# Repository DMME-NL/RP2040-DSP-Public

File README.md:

# 🎸✨ RP2040-DSP: Multi-Effect 24-bit Audio Processor

## 🧩 Summary

RP2040-DSP is a fully modular 24-bit stereo audio effects processor built on the Raspberry Pi RP2040 microcontroller. It is designed to run real-time audio effects for guitar and other instruments, including cabinet simulation for headphone or direct recording use.

The firmware architecture is modular, supporting multiple effects that can be stacked and configured flexibly.

---

## 🎛️ Features & Functionality

- **24-bit stereo signal path** at 48 kHz.
- **Up to 3 simultaneous effects**, each fully configurable and ordered in series.
- Modular effect system with easy header-based integration.
- Real-time parameter control via 6 potentiometers and rotary encoder.
- OLED display for clear feedback and editing.
- Footswitch-controlled bypass and slot toggling.
- Tap-tempo support for modulation and delay-based effects.
- VU meter and signal level visualization.
- Two expression pedal inputs:
  - One dedicated to master volume.
  - One assignable to any effect parameter.

> **Note:** Total number of simultaneous effects is limited by to CPU resources and their type.
> Some features, like MIDI and expression pedal, have not been implemented as of now.

---

## 🎚️ Available Effects

### Modulation

- **Chorus:** 1, 2, or 3 short modulated delay lines with optional stereo spread via phase offset.
- **Flanger:** Single short modulated delay with optional stereo phase offset.
- **Phaser:** Multi-stage all-pass filter network with optional stereo phase offset.
- **Tremolo:** Stereo amplitude modulation with optional stereo phase offset.

### Time-based

- **Delay:** Long stereo delay with different signal path and feedback modes, uses SPI RAM buffering. 
- **Reverb:** Hall / room type reverb based on comb and all-pass filters with modualr buffer size.

### Tone shaping

- **EQ:** Multi-band EQ similar to a guitar tone-stack. Includes range control for mid frequency.

### Dynamic

- **Compressor:** Adjustable threshold, ratio, attack, release, and makeup gain.
- **Distortion, Overdrive, Fuzz:** Various analog-inspired waveshaping algorithms with tone filtering similar to the EQ.

### Speaker & Preamp simulation

- **Cabinet Sim (Speaker Sim):** Parametric approximation of guitar cabinet. Includes multiple controls for tone shaping.
- **Preamp:** Simulates preamp coloration and dynamic shaping (Marshall, VOX, Fender).

### Work-in-Progress

- **Vibrato:** Pure pitch modulation using short-time delay interpolation.

---

## ⚡ Software Architecture and Design Choices

- **Header-based modularity:** Each effect is self-contained in its own header file (`*.h`), following a consistent structure:
  - `init_*()`
  - `load_*_parms_from_memory()`
  - `update_*_params_from_pots()`
  - `process_audio_*_sample()`
- **Pot and memory sync:** Parameters load from stored memory and dynamically update when pots change. Holding down the TAP button for 5 seconds stores all the effects and settings to flash, so they can be receovered after power-down.
- **Optimized math:** Using fixed point math and lightweight approximations, reducing CPU usage without harming audio quality.
- **Dual-core structure:**
  - **Core 0:** Dedicated to real-time audio sample processing.
  - **Core 1:** Handles UI, pot reading, OLED updates.
- **SPI RAM (APS6404L):** Used for long delay lines, minimizing local RAM usage.

> **Note:** I am an embedded electronics engineer and this is my first large software project in C.
> - *.c files frustrate me because I always forget to change them after modifying a header...
> - There will be some dependencies between variabled defined and used in different *.h header files.
> - I am using global variables in places where I might not need them / should not use them. 
> - There will be inconsistencies in coding style and methods as I have been learning a lot during the course of this project.
> - This has been some journey! I intend to clean up the code once all the features are there (I promisse...)
> - I will likely forget to clean up the code, and continue development on the newer hardware versions / platforms instead...

---

## 💻 CPU Usage (250 MHz OC, 48 kHz stereo)

| Effect        | CPU Peak Usage (%) |
|---------------|--------------------|
| Chorus        | 21%    |
| Compressor    | 11%    |
| Delay         | 49%    |
| Distortion    | 19%    |
| EQ            | 14%    |
| Flanger       | 18%    |
| Fuzz          | 24%    |
| Overdrive     | 24%    |
| Phaser        | 30%    |
| Preamp        | 52%    |
| Reverb        | 55%    |
| Speaker Sim   | 25%    |
| Tremolo       | 5%     |
| Vibrato       | WIP    |

> **Note:** Figures above are with common effects (overdrive, preamp, etc..) processed in mono.
> All effects can be processed as fully stereo by chaging the STEREO definition in the main.c file.
> Actual performace allows the Reveb and Delay to run simultaneously depending on the sample buffer size!
---

## 🖥️ User Interface Overview

- Parameter abbreviation display with full name and value popup on change.
- Encoder-controlled effect slot assignment and navigation.
- LED blink feedback for modulation or delays.
- Footswitch toggling per effect slot, with LED status indication.
- VU meter visualizing signal levels or compressor gain reduction in real time.
- Delay UI with time settings in [ms] or tap-tempo with selectable fractions.

---

## 🔧 Hardware Overview

> Version 1.2

This design can be ordered directly from PCBWay, including assembly of the SMD components.
See the hardware folders for a complete bill of materials (ibom.html) that also includes all the modules and THT parts. 
If you do not want to use PCBway, or refuse to give me the please of a small 10% commision via their services; the KiCAD project, gerbers, and BOM are also located in this repository.

PCBway profile: https://www.pcbway.com/project/member/?bmbno=88DFECEC-9511-40

Mainboard V1.2:  https://www.pcbway.com/project/shareproject/RP2040_Multi_effect_Pedal_Mainboard_30e99e7d.html

Mainboard V2.1:  https://www.pcbway.com/project/shareproject/RP2040_Multi_effect_Pedal_Mainboard_V2_1_08d54258.html

Daughterboard:  https://www.pcbway.com/project/shareproject/RP2040_Multi_effect_Pedal_Daughterboard_25cda6b7.html

- **ADC:** PCM1808 stereo ADC module.
- **DAC:** PCM5102 stereo DAC module.
- **Regulated power:** LM78xx linear regulators.
- **Form factor:** Designed for Hammond 1950DD enclosure.
- **Input voltage:** 9–12 V DC.
- **Expression pedals:** 2 inputs, configurable.

❗NOTE: PCM1808 inputs are not attenuated and will clip with high-output pickups. The ADC has an input RC filter on-board that can be replaced by a ~100k series resistance to provide ~2x attenuation.

> **Later versions:**  PCM3060 version are have not yet been fully tested!. The concept was proven on a different PCB design and identical schematic - without any changes to the software. Although, I did not test this PCB design specificaly, it should work perfectly fine.

---

## 📜 License

The full text of the license should be found in LICENSE.txt, included as part of this repository.

This library and all accompanying code, examples, information and documentation is Copyright (C) 2025 Milan Wendt

This program is free software: you can redistribute it and/or modify it under the terms of the GNU General Public
License, version 3 as published by the Free Software Foundation.

This program is distributed in the hope that it will be useful, but WITHOUT ANY WARRANTY; without even the implied
warranty of MERCHANTABILITY or FITNESS FOR A PARTICULAR PURPOSE. See the GNU General Public License for more details.

You should have received a copy of the GNU General Public License along with this program. If not,
see <https://www.gnu.org/licenses/>.

---

🎸 Enjoy building and tweaking your own ultimate guitar multi-effects processor with RP2040-DSP!

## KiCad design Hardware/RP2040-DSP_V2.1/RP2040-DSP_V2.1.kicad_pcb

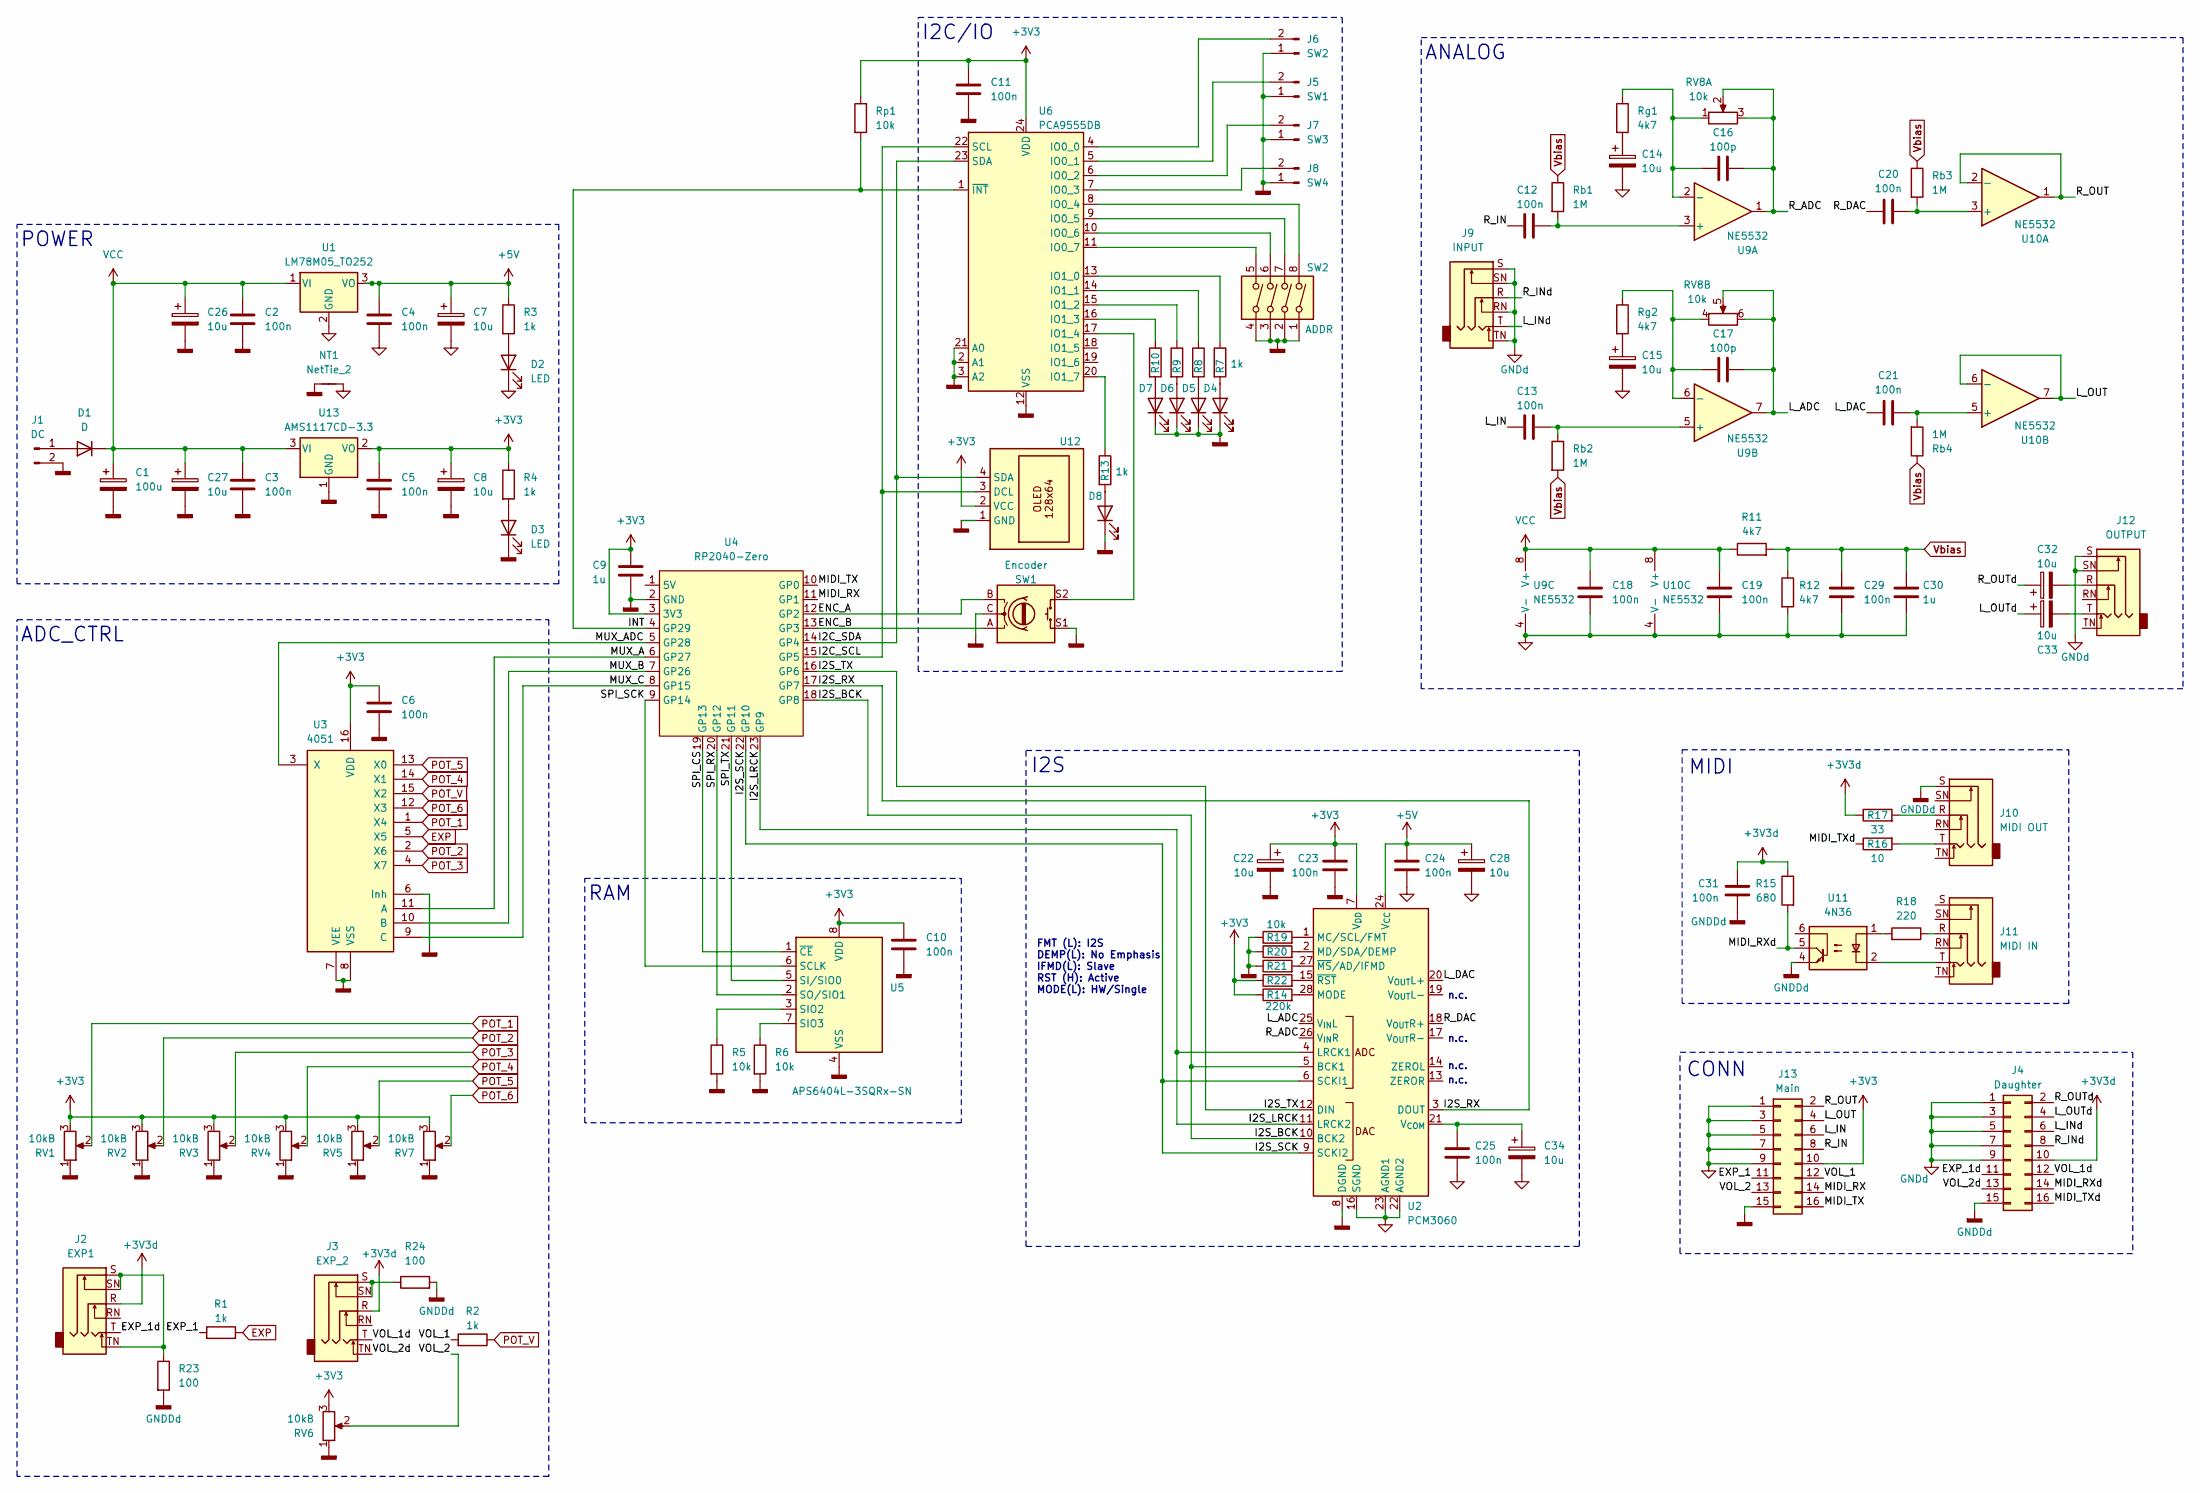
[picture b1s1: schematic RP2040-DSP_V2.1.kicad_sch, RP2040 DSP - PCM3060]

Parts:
C1: 100u; C_Elec_6.3x5.8
C2, C3, C4, C5, C6, C10, C11, C12, C13, C18, C19, C20, C21, C23, C24, C25, C29, C31: 100n; C_0805_2012Metric
C7, C8, C14, C15, C22, C26, C27, C28, C32, C33, C34: 10u; C_Elec_4x5.4
C9, C30: 1u; C_0805_2012Metric
C16, C17: 100p; C_0805_2012Metric
D1: D; D_0805_2012Metric
D2, D3: LED; D_0805_2012Metric
D4, D5, D6, D7, D8: LED; LED_D5.0mm
J1: DC; PinHeader_1x02_P2.54mm_Vertical
J2: EXP1; Jack 6.35mm Horizontal
J3: EXP_2; Jack 6.35mm Horizontal
J4: Daughter; IDC-Header_2x08_P2.54mm_Vertical
J5: SW1; PinHeader_1x02_P2.54mm_Vertical
J6: SW2; PinHeader_1x02_P2.54mm_Vertical
J7: SW3; PinHeader_1x02_P2.54mm_Vertical
J8: SW4; PinHeader_1x02_P2.54mm_Vertical
J9: INPUT; Jack 6.35mm Horizontal
J10: MIDI OUT; Jack 6.35mm Horizontal
J11: MIDI IN; Jack 6.35mm Horizontal
J12: OUTPUT; Jack 6.35mm Horizontal
J13: Main; IDC-Header_2x08_P2.54mm_Vertical
NT1: NetTie_2; NetTie-2_SMD_Pad2.0mm
R1, R2, R3, R4, R7, R8, R9, R10, R13: 1k; R_0805_2012Metric
R5, R6, R19, R20, R21, R22: 10k; R_0805_2012Metric
R11, R12: 4k7; R_0805_2012Metric
R14: 220k; R_0805_2012Metric
R15: 680; R_0805_2012Metric
R16: 10; R_0805_2012Metric
R17: 33; R_0805_2012Metric
R18: 220; R_0805_2012Metric
R23, R24: 100; R_0805_2012Metric
RV1, RV2, RV3, RV4, RV5, RV6, RV7: 10kB; Potentiometer_Alpha_RD901F-40-00D
RV8: 10k; Potentiometer_Alpha_RD902F-40-00D
Rb1, Rb2, Rb3, Rb4: 1M; R_0805_2012Metric
Rg1, Rg2: 4k7; R_0805_2012Metric
Rp1: 10k; R_0805_2012Metric
SW1: Encoder; RotaryEncoder_Alps_EC11
SW2: ADDR; SW_DIP_SPSTx04_Slide_9.78x12.34mm_W7.62mm_P2.54mm
U1: LM78M05_TO252; TO-252-2
U2: PCM3060; TSSOP-28_4.4x9.7mm_P0.65mm
U3: 4051; TSSOP-16_4.4x5mm_P0.65mm
U4: RP2040-Zero; RP2040 Zero Header
U5: APS6404L-3SQRx-SN; SOIC-8_3.9x4.9mm_P1.27mm
U6: PCA9555DB; SSOP-24_5.3x8.2mm_P0.65mm
U9, U10: NE5532; SOIC-8_3.9x4.9mm_P1.27mm
U11: 4N36; DIP-6_W7.62mm
U12: 128x64OLED
U13: AMS1117CD-3.3; TO-252-3_TabPin2

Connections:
+3V3: C5.1, C6.1, C8.1, C9.1, C10.1, C11.1, C22.1, C23.1, J13.10, R4.1, R14.1, R22.1, RV1.3, RV2.3, RV3.3, RV4.3, RV5.3, RV6.3, RV7.3, Rp1.1, U2.7 (V_{DD}), U3.16 (VDD), U4.3 (3V3), U5.8 (VDD), U6.24 (VDD), U12.2 (VCC), U13.2 (VO)
+3V3d: C31.1, J2.R, J3.R, J4.10, R15.1, R17.1
+5V: C4.1, C7.1, C24.1, C28.1, R3.1, U1.3 (VO), U2.24 (V_{CC})
/ENC_A: SW1.B, U4.12 (GP2)
/ENC_B: SW1.A, U4.13 (GP3)
/EXP_1: J13.11, R1.2
/EXP_1d: J2.T, J4.11
/I2C_SCL: U4.15 (GP5), U6.22 (SCL), U12.3 (DCL)
/I2C_SDA: U4.14 (GP4), U6.23 (SDA), U12.4 (SDA)
/I2S_BCK: U2.5 (BCK1), U2.10 (BCK2), U4.18 (GP8)
/I2S_LRCK: U2.4 (LRCK1), U2.11 (LRCK2), U4.23 (GP9)
/I2S_RX: U2.3 (DOUT), U4.17 (GP7)
/I2S_SCK: U2.6 (SCKI1), U2.9 (SCKI2), U4.22 (GP10)
/I2S_TX: U2.12 (DIN), U4.16 (GP6)
/INT: Rp1.2, U4.4 (GP29), U6.1 (~INT)
/L_ADC: C17.1, RV8.5, RV8.6, U2.25 (V_{IN}L), U9.7
/L_DAC: C21.1, U2.20 (V_{OUT}L+)
/L_IN: C13.1, J13.6
/L_INd: J4.6, J9.T
/L_OUT: J13.4, U10.6 (-), U10.7
/L_OUTd: C33.1, J4.4
/MIDI_RX: J13.14, U4.11 (GP1)
/MIDI_RXd: J4.14, R15.2, U11.5
/MIDI_TX: J13.16, U4.10 (GP0)
/MIDI_TXd: J4.16, R16.1
/MUX_A: U3.11 (A), U4.6 (GP27)
/MUX_ADC: U3.3 (X), U4.5 (GP28)
/MUX_B: U3.10 (B), U4.7 (GP26)
/MUX_C: U3.9 (C), U4.8 (GP15)
/R_ADC: C16.1, RV8.2, RV8.3, U2.26 (V_{IN}R), U9.1
/R_DAC: C20.1, U2.18 (V_{OUT}R+)
/R_IN: C12.1, J13.8
/R_INd: J4.8, J9.R
/R_OUT: J13.2, U10.1, U10.2 (-)
/R_OUTd: C32.1, J4.2
/SPI_CS: U4.19 (GP13), U5.1 (~CE)
/SPI_RX: U4.20 (GP12), U5.2 (SO/SIO1)
/SPI_SCK: U4.9 (GP14), U5.6 (SCLK)
/SPI_TX: U4.21 (GP11), U5.5 (SI/SIO0)
/VOL_1: J13.12, R2.2
/VOL_1d: J3.T, J4.12
/VOL_2: J13.13, RV6.2
/VOL_2d: J3.TN, J4.13
EXP: R1.1, U3.5 (X5)
GND: C4.2, C7.2, C14.2, C15.2, C18.2, C19.2, C24.2, C25.2, C28.2, C29.2, C30.2, C34.2, D2.1 (K), J13.1, J13.3, J13.5, J13.7, J13.9, NT1.2, R12.2, U1.2 (GND), U2.16 (SGND), U2.22 (AGND2), U2.23 (AGND1), U9.4 (V-), U10.4 (V-)
GNDD: C1.2, C2.2, C3.2, C5.2, C6.2, C8.2, C9.2, C10.2, C11.2, C22.2, C23.2, C26.2, C27.2, D3.1 (K), D4.1 (K), D5.1 (K), D6.1 (K), D7.1 (K), D8.1 (K), J1.2, J5.1, J6.1, J7.1, J8.1, J13.15, NT1.1, R5.2, R6.2, R19.1, R20.1, R21.1, RV1.1, RV2.1, RV3.1, RV4.1, RV5.1, RV6.1, RV7.1, SW1.C, SW1.MP, SW1.S1, SW2.1, SW2.2, SW2.3, SW2.4, U2.8 (DGND), U3.6 (Inh), U3.7 (VEE), U3.8 (VSS), U4.2 (GND), U5.4 (VSS), U6.2 (A1), U6.3 (A2), U6.12 (VSS), U6.21 (A0), U12.1 (GND), U13.1 (GND)
GNDd: J4.1, J4.3, J4.5, J4.7, J4.9, J9.RN, J9.S, J9.SN, J9.TN, J12.S, J12.SN
unnamed: C14.1, Rg1.2
unnamed: C15.1, Rg2.2
unnamed: C32.2, J12.R
unnamed: C33.2, J12.T
unnamed: D1.2 (A), J1.1
unnamed: D2.2 (A), R3.2
unnamed: D3.2 (A), R4.2
unnamed: D4.2 (A), R7.2
unnamed: D5.2 (A), R8.2
unnamed: D6.2 (A), R9.2
unnamed: D7.2 (A), R10.2
unnamed: D8.2 (A), R13.2
unnamed: J5.2, U6.5 (IO0_1)
unnamed: J6.2, U6.4 (IO0_0)
unnamed: J7.2, U6.6 (IO0_2)
unnamed: J8.2, U6.7 (IO0_3)
unnamed: J10.R, R17.2
unnamed: J10.T, R16.2
unnamed: J11.R, R18.1
unnamed: J11.T, U11.2
unnamed: R18.2, U11.1
unnamed: R19.2, U2.1 (MC/SCL/FMT)
unnamed: R20.2, U2.2 (MD/SDA/DEMP)
unnamed: R14.2, U2.28 (MODE)
unnamed: C25.1, C34.1, U2.21 (V_{COM})
unnamed: R21.2, U2.27 (~MS/AD/IFMD)
unnamed: R22.2, U2.15 (~RST)
unnamed: R5.1, U5.3 (SIO2)
unnamed: R6.1, U5.7 (SIO3)
unnamed: SW2.8, U6.8 (IO0_4)
unnamed: SW2.7, U6.9 (IO0_5)
unnamed: SW2.6, U6.10 (IO0_6)
unnamed: SW2.5, U6.11 (IO0_7)
unnamed: R7.1, U6.13 (IO1_0)
unnamed: R8.1, U6.14 (IO1_1)
unnamed: R9.1, U6.15 (IO1_2)
unnamed: R10.1, U6.16 (IO1_3)
unnamed: SW1.S2, U6.17 (IO1_4)
unnamed: R13.1, U6.20 (IO1_7)
unnamed: C12.2, Rb1.2, U9.3 (+)
unnamed: C16.2, RV8.1, Rg1.1, U9.2 (-)
unnamed: C13.2, Rb2.1, U9.5 (+)
unnamed: C17.2, RV8.4, Rg2.1, U9.6 (-)
unnamed: C20.2, Rb3.2, U10.3 (+)
unnamed: C21.2, Rb4.2, U10.5 (+)
POT_1: RV1.2, U3.1 (X4)
POT_2: RV2.2, U3.2 (X6)
POT_3: RV3.2, U3.4 (X7)
POT_4: RV4.2, U3.14 (X1)
POT_5: RV5.2, U3.13 (X0)
POT_6: RV7.2, U3.12 (X3)
POT_V: R2.1, U3.15 (X2)
VCC: C1.1, C2.1, C3.1, C18.1, C19.1, C26.1, C27.1, D1.1 (K), R11.1, U1.1 (VI), U9.8 (V+), U10.8 (V+), U13.3 (VI)
Vbias: C29.1, C30.1, R11.2, R12.1, Rb1.1, Rb2.2, Rb3.1, Rb4.1

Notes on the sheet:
ANALOG
n.c.
MIDI
ADC_CTRL
RAM
CONN
FMT (L): I2S DEMP(L): No Emphasis IFMD(L): Slave RST (H): Active MODE(L): HW/Single
POWER
I2C/IO
I2S

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
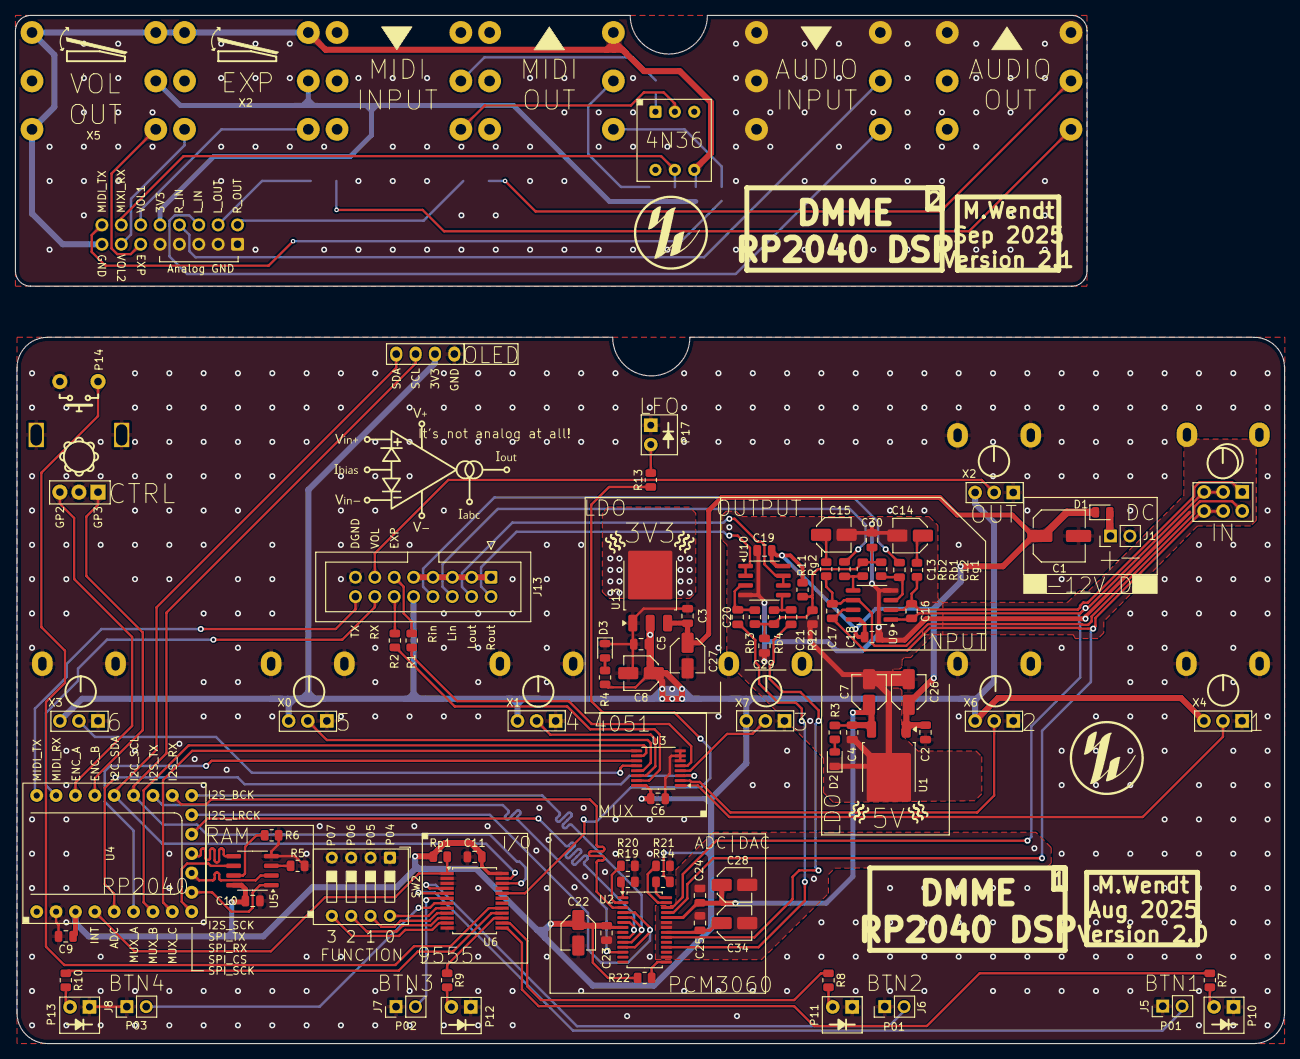
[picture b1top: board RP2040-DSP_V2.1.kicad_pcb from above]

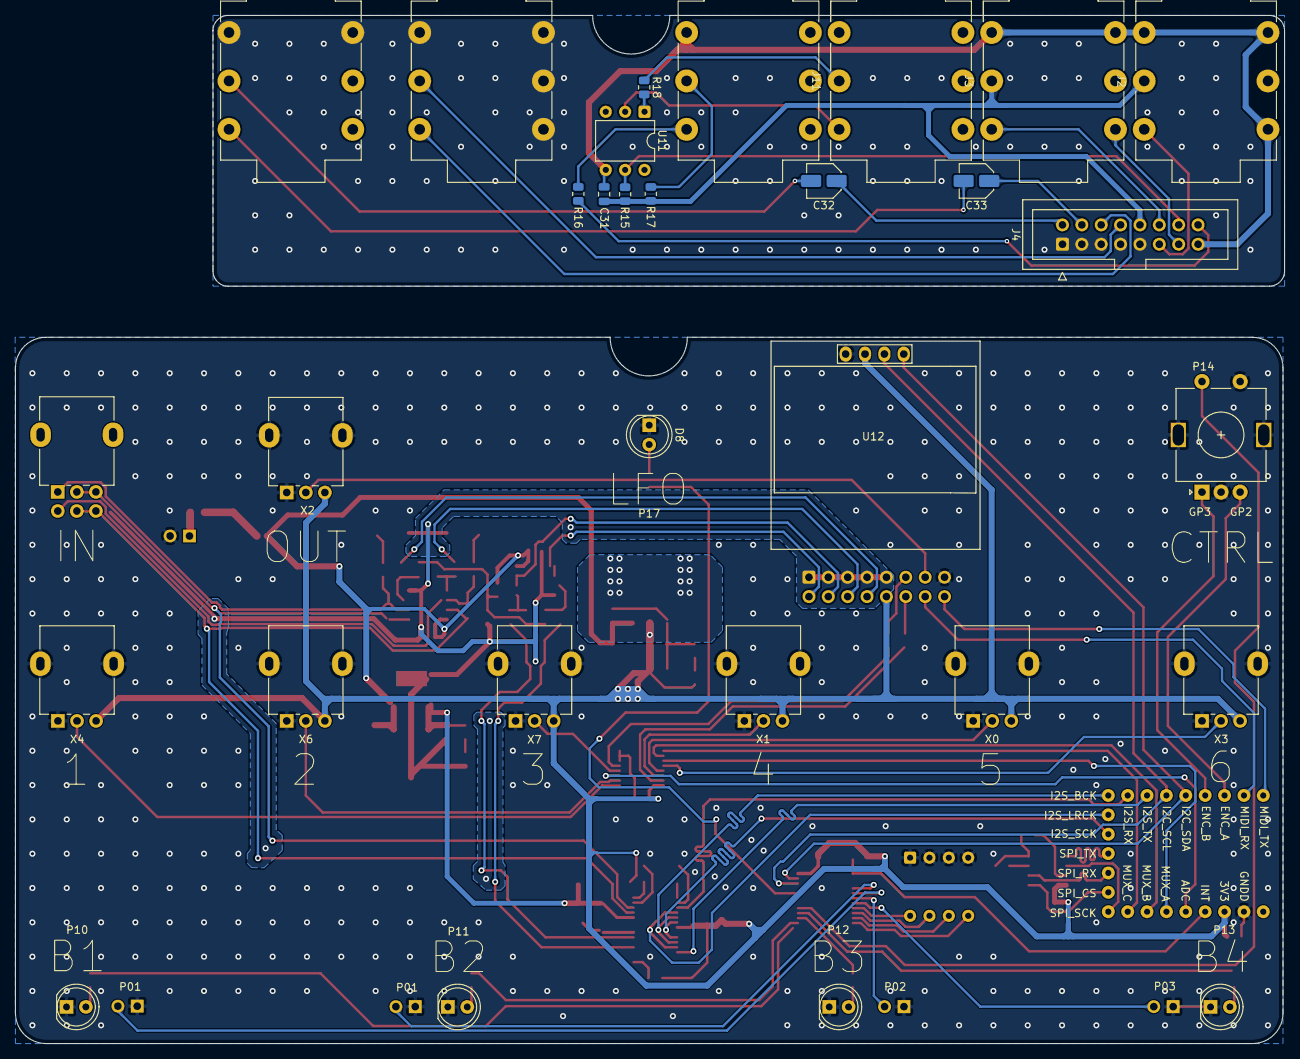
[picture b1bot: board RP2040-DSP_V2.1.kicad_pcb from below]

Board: 2 copper layers, 166.4 x 134.8 mm, 106 parts (30 on the bottom side), 102 nets.

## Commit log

2025-08-19 [Initial Release] Working, but still a long road ahead!
2025-08-19 Update README.md
    [DOC] Added render of the enclosure and PCB
2025-08-21 [HW] Included V2.0 version of PCB with PCM3060 instead of modules.
    Updated V1.0 to V1.1 with Via stitching and Gnd plane modifications.
2025-08-22 [PREAMP] Added preamp models for Fender, Vox, Marshall, Soldano
    [STEREO] Added optional setting for Mono | Stereo for all gain and dynamic effects to save CPU
    [I2S] changed buffer size for testing
    Included some helpers for frequency calculation from analog circuits.
    Decided to not go that far into modeling amps to save CPU..
2025-09-03 Update:
    - Flash storage implemented for saving settings
    - Tap button hold (5sec) saves settings fopr next boot
    - Tap tempo implemented for delay
    - Fractions implemented for delay tap tempo
    - LEDs blink according to delay time
    - Optimized compiler and memory for pre-amps
2025-09-06 Update README.md
    Latest software updates included
2025-09-07 [FIX] interpolation noise from chorus and flanger fixed
    [OPT] Delay and reverb option to support tails when disabled
    [Flash] Fixed memory sometimes getting initialized as zeros
2025-09-08 [PCB] Swapped inputs / outputs so the connections are in line with normal guitar pedal
2025-09-08 [3D] Models updated
2025-09-11 Added manufacturing files and BOM for V1.2
2025-09-11 Update README.md
    links to PCBway added
2025-09-11 THT bom with Aliexpress links added
2025-09-11 V2.1 assembly files added
2025-09-11 Document for V1.2 ADC module issue added
